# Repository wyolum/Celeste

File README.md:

Celeste
=======

decorative celestial clock

License
-------
[CERN Open Hardware Licence v1.2 ]

[CERN Open Hardware Licence v1.2 ]:http://www.ohwr.org/attachments/2388/cern_ohl_v_1_2.txt

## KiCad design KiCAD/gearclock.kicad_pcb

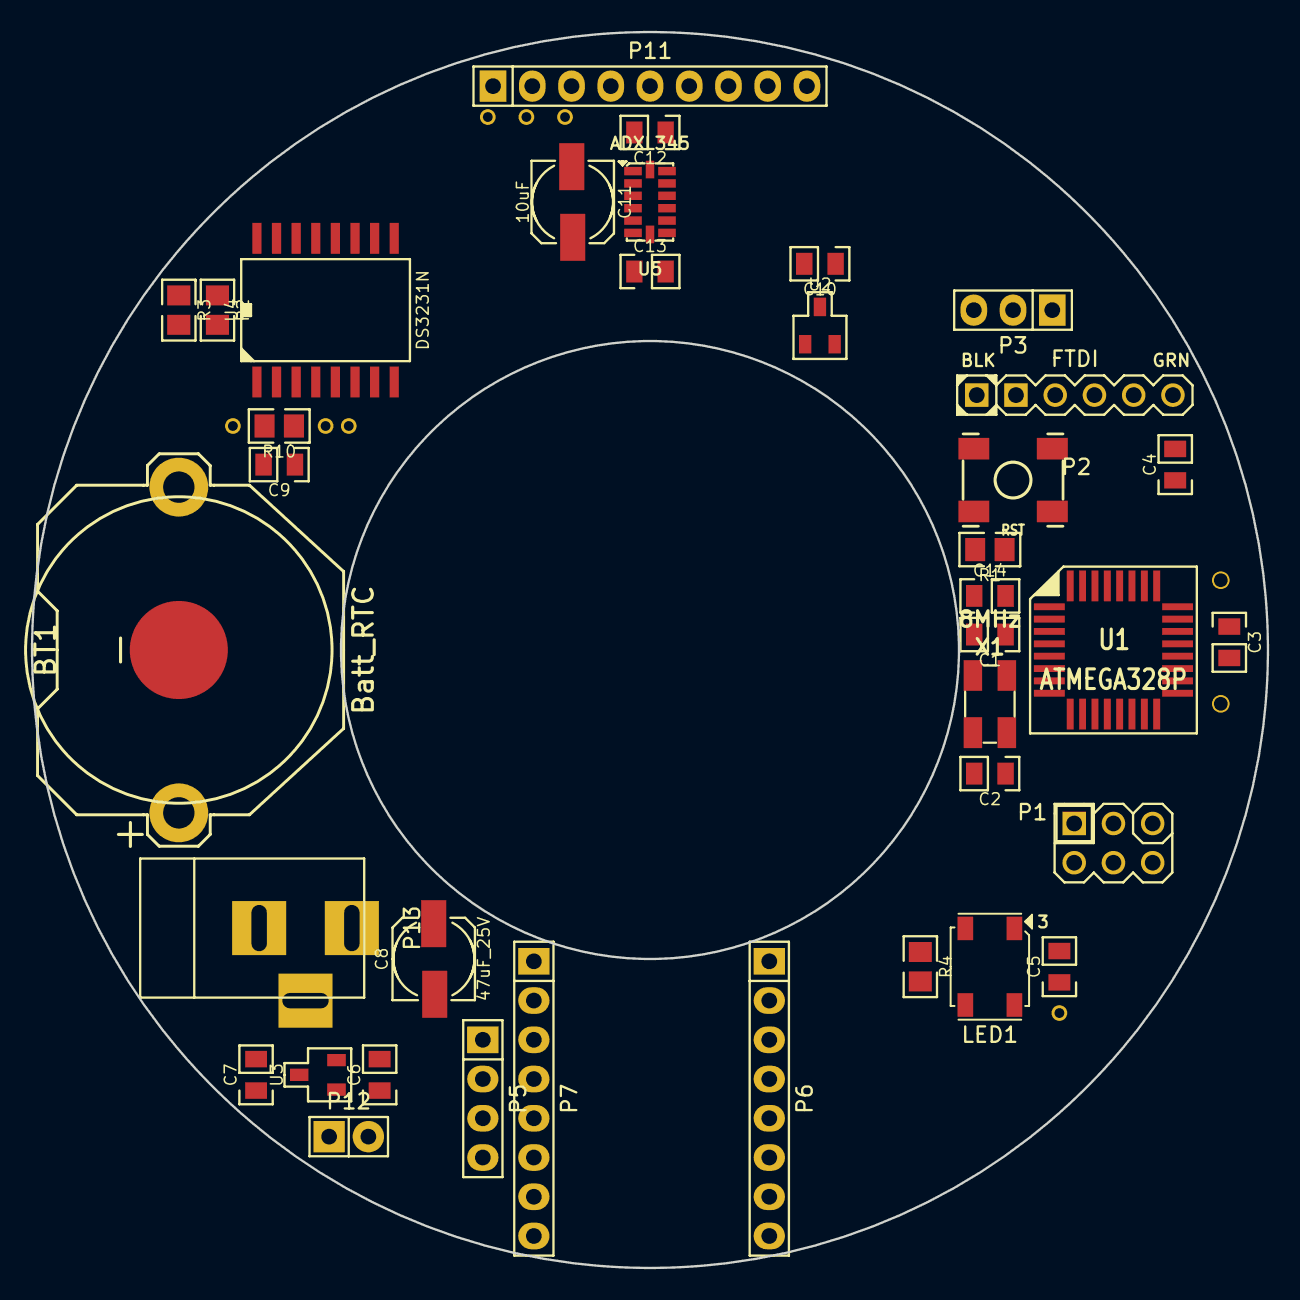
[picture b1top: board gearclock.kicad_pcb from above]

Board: 2 copper layers, 80.0 x 80.0 mm, 45 parts (1 on the bottom side), 40 nets, no tracks yet.

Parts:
B1, B2, B3, B4: IO
BT1: Batt_RTC; CR2032
C1, C2: 22p; c_0805
C3, C4, C5, C9, C10, C14: 100n; c_0805
C6, C7: 1u; c_0805
C8: 47uF_25V; C_ELCO_SMD
C11: 10uF; C_ELCO_SMD
C12, C13: 100nF; c_0805
LED1: WS2812B; RGB_WS2811B
P1: ISP; Header_ISP
P2: FTDI; Header_FTDI
P3: SW_EXT; Pin_Header_Straight_1x03
P5: Motor; Pin_Header_Straight_1x04
P6: Motor_R; Pin_Header_Straight_1x08
P7: Motor_L; Pin_Header_Straight_1x08
P8, P9, P10: IO
P11: GPS; Pin_Header_Straight_1x09
P12: 3V3_In; Pin_Header_Straight_1x02
P13: WallW; BARREL_JACK
R1, R2, R3, R10: 10k; r_0805
R4: 750E; r_0805
SD1: SD_CARD_Micro; SD_Micro
SW1: RST; Switch_SMT
U1: ATMEGA328P; TQFP32
U2: Hall_Sensor; SOT23-3
U3: 3V3; SOT23-3
U4: DS3231N; DS3231
U5: ADXL345
X1: 8MHz; Xtal_SMD4

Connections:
+3.3V: C3.1, C6.1, C10.1, C11.1, C12.1, C13.1, C14.1, P1.2, P2.3, P3.1, P6.6, P11.8, P12.1, R1.1, R2.1, R3.1, R10.1, SD1.4, U1.4, U1.6, U1.18, U1.20, U2.1, U3.2, U4.2, U5.1, U5.6, U5.7
/1pps: P11.9, U1.32
/3Vgps: P8.1, P11.1
/5V: C5.1, C7.1, C8.1, LED1.3, P7.1, P13.2, U3.3
/A1: P5.3, P7.5
/A2: P5.4, P7.6
/B1: P5.2, P7.4
/B2: P5.1, P7.3
/DIR: P6.8, U1.13
/EN: P6.1, U1.12
/FIX: P11.4, U1.19
/GPS_BAT: P10.1, P11.3
/GPS_EN: P9.1, P11.2, U1.23
/GPS_Rx: P11.6, U1.9
/GPS_Tx: P11.5, U1.10
/Hall: U1.22, U2.2
/LED1: R4.2, U1.11
/M0: P6.2, U1.24
/M1: P6.3, U1.25
/MISO: P1.1, SD1.7, U1.16
/MOSI: P1.4, SD1.3, U1.15
/PB6: C1.1, U1.7, X1.1
/PB7: C2.2, U1.8, X1.2
/RESET: C4.2, P1.5, R1.2, SW1.2, U1.29
/RXD: P2.4, U1.30
/SCK: P1.3, SD1.5, U1.17
/SS: SD1.2, U1.14
/STP: P6.7, U1.2
/SW: P3.2, U1.26
/TXD: P2.5, U1.31
/gearclock_rtc/32k: B4.1, U4.1
/gearclock_rtc/BAT: BT1.+, C9.1, U4.14
/gearclock_rtc/RST: B3.1, U4.4
/gearclock_rtc/SCL: R3.2, U1.28, U4.16, U5.14
/gearclock_rtc/SDA: R2.2, U1.27, U4.15, U5.13
/gearclock_rtc/SQW: B2.1, R10.2, U1.1, U4.3
GND: BT1.-, C1.2, C2.1, C3.2, C5.2, C6.2, C7.2, C8.2, C9.2, C10.2, C11.2, C12.2, C13.2, C14.2, LED1.1, P1.6, P2.1, P2.2, P3.3, P7.2, P7.8, P11.7, P12.2, P13.1, SD1.6, SD1.G1, SD1.G2, SD1.G3, SD1.G4, SW1.1, U1.3, U1.5, U1.21, U2.3, U3.1, U4.5, U4.6, U4.7, U4.8, U4.9, U4.10, U4.11, U4.12, U4.13, U5.2, U5.4, U5.5, U5.12, X1.3
unnamed: B1.1, LED1.2
unnamed: C4.1, P2.6
unnamed: LED1.4, R4.1

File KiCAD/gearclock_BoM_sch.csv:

Reference, Value, Footprint, Datasheet, Digikey, Part No, Field4, Field5, Field6, Field7, Field8, Field9, Field10, Field11
C2,22p,gearclock_fp:c_0805,,490-1734-1-ND,,,,,,,,,
C1,22p,gearclock_fp:c_0805,,490-1734-1-ND,,,,,,,,,
C6,1u,gearclock_fp:c_0805,
R4,750E,gearclock_fp:r_0805,
C4,100n,gearclock_fp:c_0805,
U3,3V3,gearclock_fp:SOT23-3,,,MCP1700T-3302E/TT,,,,,,,,
R2,10k,gearclock_fp:r_0805,
R3,10k,gearclock_fp:r_0805,
SW1,RST,gearclock_fp:Switch_SMT,,,,,,,,,,,
R1,10k,gearclock_fp:r_0805,
C3,100n,gearclock_fp:c_0805,
C7,1u,gearclock_fp:c_0805,
X1,8MHz,gearclock_fp:Xtal_SMD4,
P8,IO,gearclock_fp:IO,
P9,IO,gearclock_fp:IO,
P10,IO,gearclock_fp:IO,
SD1,SD_CARD_Micro,gearclock_fp:SD_Micro,
C8,47uF_25V,gearclock_fp:C_ELCO_SMD,
U2,Hall_Sensor,gearclock_fp:SOT23-3,
U1,ATMEGA328P,gearclock_fp:TQFP32,
C5,100n,gearclock_fp:c_0805,,,,CAP CER 0.1UF 25V 10% X7R 0805,100nF, 25V,Surface Mount, MLCC,Kemet,C0805C104K3RACTU,Digikey,399-1168-1-ND,http://www.digikey.com/product-detail/en/C0805C104K3RACTU/39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
LED1,WS2812B,gearclock_fp:RGB_WS2811B,
B1,IO,gearclock_fp:IO,
C10,100n,gearclock_fp:c_0805,,,,CAP CER 0.1UF 25V 10% X7R 0805,100nF, 25V,Surface Mount, MLCC,Kemet,C0805C104K3RACTU,Digikey,399-1168-1-ND,http://www.digikey.com/product-detail/en/C0805C104K3RACTU/39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
P1,ISP,gearclock_fp:Header_ISP,
P2,FTDI,gearclock_fp:Header_FTDI,
P7,Motor_L,gearclock_fp:Pin_Header_Straight_1x08,
P6,Motor_R,gearclock_fp:Pin_Header_Straight_1x08,
P11,GPS,gearclock_fp:Pin_Header_Straight_1x09,
P5,Motor,gearclock_fp:Pin_Header_Straight_1x04,
P12,3V3_In,gearclock_fp:Pin_Header_Straight_1x02,
P13,WallW,gearclock_fp:BARREL_JACK,
P3,SW_EXT,gearclock_fp:Pin_Header_Straight_1x03,
U5,ADXL345,gearclock_fp:ADXL345,
C12,100nF,gearclock_fp:c_0805,,,,CAP FILM 0.1UF 63VDC RADIAL,100nF, 63V,R82,Kemet,R82DC3100AA50J,Digikey,399-5863-ND,http://www.digikey.com/product-detail/en/R82DC3100AA50J/399-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
C13,100nF,gearclock_fp:c_0805,,,,CAP FILM 0.1UF 63VDC RADIAL,100nF, 63V,R82,Kemet,R82DC3100AA50J,Digikey,399-5863-ND,http://www.digikey.com/product-detail/en/R82DC3100AA50J/399-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
C11,10uF,gearclock_fp:C_ELCO_SMD,,,,CAP ALUM 100UF 16V 20% RADIAL,100u,16V,Radial, Can, 6.3mm dia,Panasonic Electronic Components,ECE-A1CKA101,Digikey,P833-ND,http://www.digikey.com/product-detail/en/ECE-A1CKA101/P833-N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
R10,10k,gearclock_fp:r_0805,
B4,IO,gearclock_fp:IO,
B3,IO,gearclock_fp:IO,
B2,IO,gearclock_fp:IO,
U4,DS3231N,gearclock_fp:DS3231,
C9,100n,gearclock_fp:c_0805,
BT1,Batt_RTC,gearclock_fp:CR2032,,BU2032SM-HD-GCT-ND ,,,,,,,,,

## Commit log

2014-02-17 initial
2014-02-17 cleaned stl files and emacs files
2014-02-17 broke out 6 tooth gear into seperate file from gear library
2014-02-17 added gear.scad as a seperate file from gear library
2014-02-23 added moon.scad
2014-03-23 added minute hand to gear
2014-03-23 added gear_clock to repo
2014-04-05 aded svg files for gear_clock2
2014-04-05 added arduino code
2014-04-26 added extra diameter to axel
2014-11-29 added hour hand
2014-11-29 minor adjustment
2014-11-29 added acrylic pieces
2014-12-18 modified inner gear, added holes
2014-12-19 added required libs
2014-12-20 added .25 inch laser cutting layer
2014-12-20 modified for laser cutting
2014-12-20 added sheet to gear clock for lasering
2014-12-22 tweaked inner_gear to spin better
2014-12-24 bored all the way though minute hand so that it can be pressed furhter in
2014-12-27 made hands thinner
2014-12-28 add filagree hands
2014-12-28 lengthed hour hand pin to accomodate new inner_gear
2014-12-29 made inner gear a bit thicker to reduce rattling
2014-12-29 now catches after power outage.
2015-01-19 added new version of GearClock Gears3
2015-01-21 added gears 3 clock
2015-01-21 schematic file
2015-01-29 added gearclock4 h:m:s clock
2015-01-29 more gear clock stuff
2015-01-30 first working version of GearClock4
2015-02-02 made all large gears out of acrylic. working version
2015-02-03 H:M:S working
2015-02-03 added laser cut parts to scad
2015-02-04 minor changes to stack
2015-02-06 clean up for kevins print
2015-02-06 added images
2015-02-08 changed filenames of images
2015-02-08 made bearing cutout 22.1mm
2015-02-08 Gear Clock schematic work in progress
2015-02-13 converting to 2x gear pitch
2015-02-15 added NOTES.txt for pcb
2015-02-22 GearClock schematic needs review
2015-02-23 GearClock schematic mods
2015-02-25 GearClock schematic update
2015-02-28 GearClock schematic work in progress
2015-06-09 review the schematic
2015-06-11 Schematic, work in progress
